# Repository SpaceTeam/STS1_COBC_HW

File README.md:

# COBC Hardware

This is a github repo for the COBC (communication and on-board computer) project of SpaceTeamSat1 (STS1) CubeSat mission of the TU Wien Space Team.

# Licensing
STS1_COBC_HW (c) by TU Wien Space Team

STS1_COBC_HW is licensed under a
Creative Commons Attribution 4.0 International License.

You should have received a copy of the license along with this
work. If not, see <https://creativecommons.org/licenses/by/4.0/>.

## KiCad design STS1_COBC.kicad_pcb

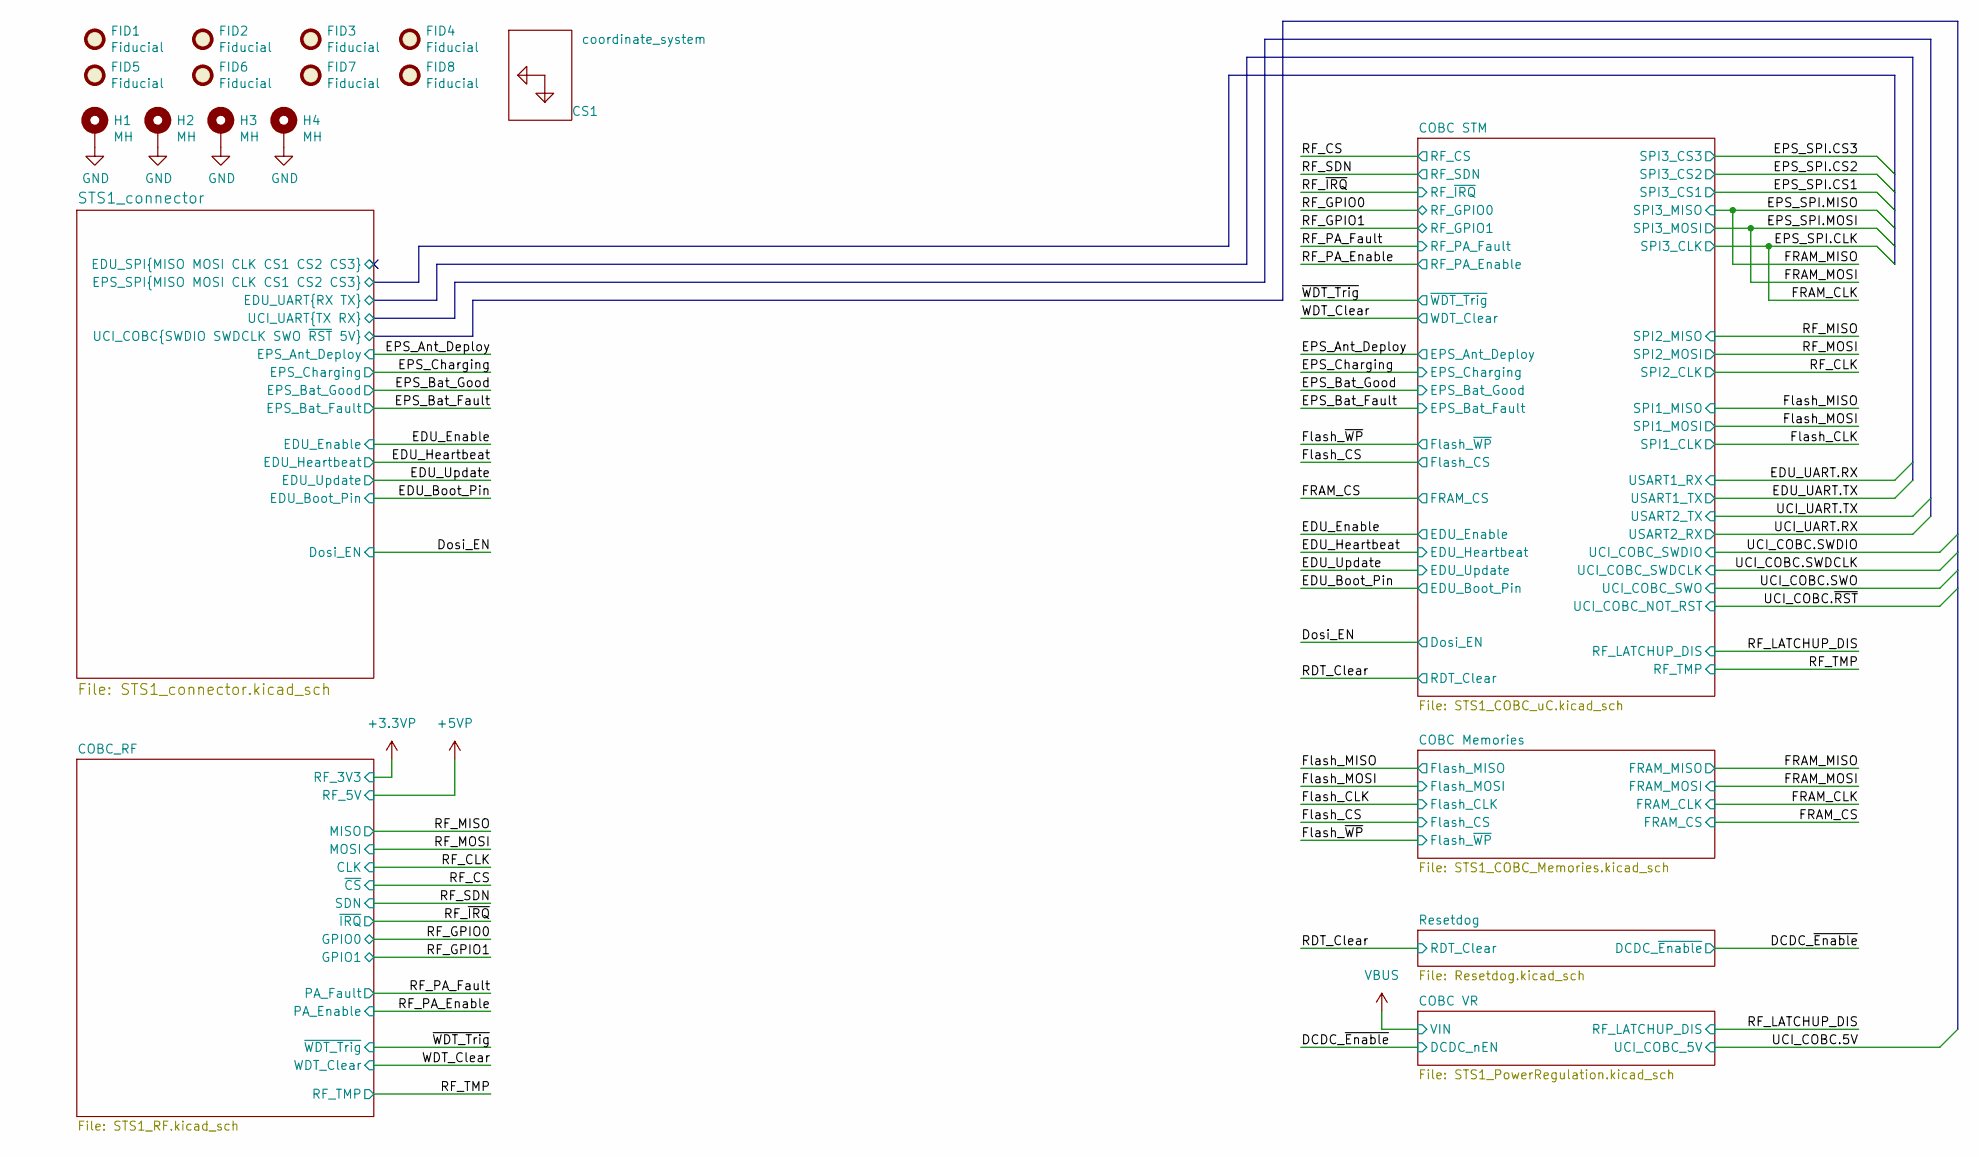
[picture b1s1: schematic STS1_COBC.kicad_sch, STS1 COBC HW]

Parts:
CS1: coordinate_system; Coordinates
FID1, FID2, FID3, FID4, FID5, FID6, FID7, FID8: Fiducial; Fiducial_0.75mm_Mask1.5mm
H1, H2, H3, H4: MH; MountingHole_4.3mm_M4_Pad_Via

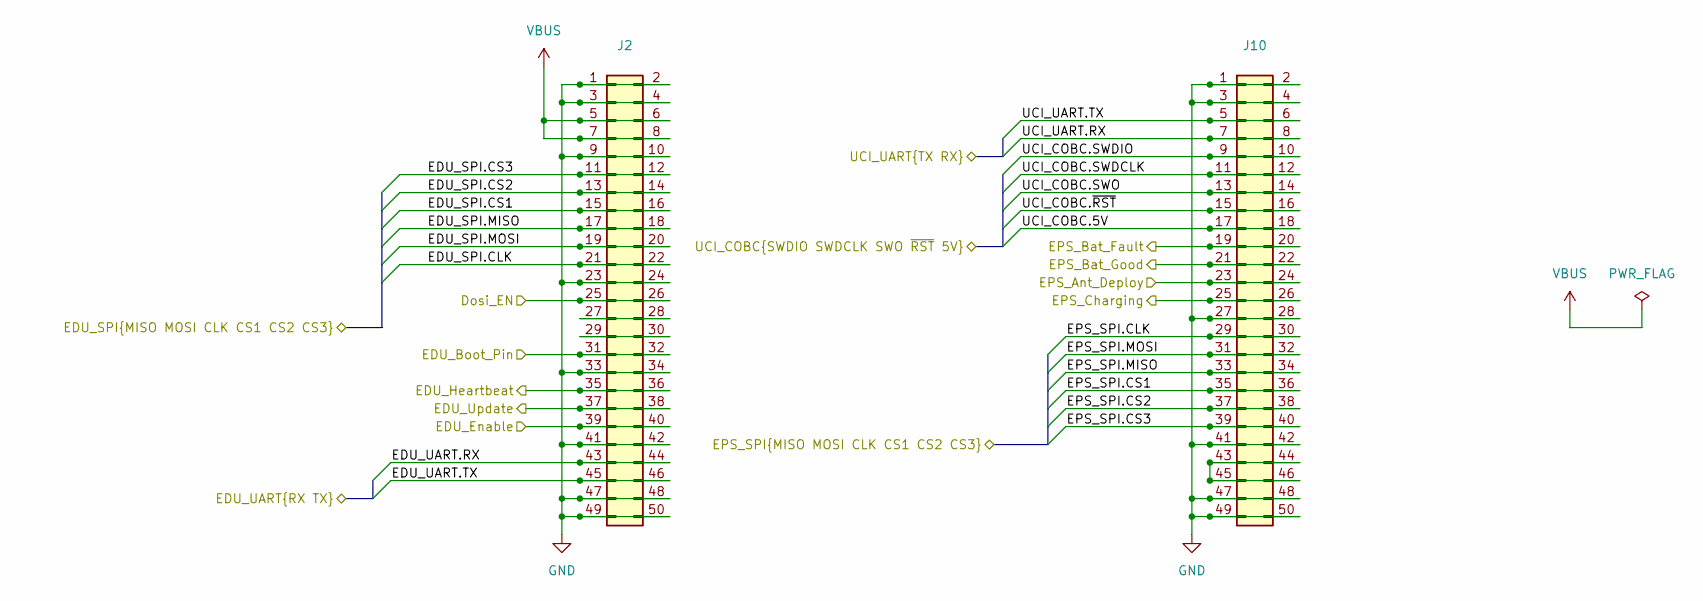
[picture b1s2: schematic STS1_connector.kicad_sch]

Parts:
J2, J10: PinSocket_2x25_P2.00mm_Vertical

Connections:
/Dosi_EN: J2.25, J2.26; also elsewhere on the board
/EDU_Boot_Pin: J2.31, J2.32; also elsewhere on the board
/EDU_Enable: J2.39, J2.40; also elsewhere on the board
/EDU_Heartbeat: J2.35, J2.36; also elsewhere on the board
/EDU_Update: J2.37, J2.38; also elsewhere on the board
/EPS_Ant_Deploy: J10.23, J10.24; also elsewhere on the board
/EPS_Bat_Fault: J10.19, J10.20; also elsewhere on the board
/EPS_Bat_Good: J10.21, J10.22; also elsewhere on the board
/EPS_Charging: J10.25, J10.26; also elsewhere on the board
/STS1_connector/EDU_SPI.CLK: J2.21, J2.22
/STS1_connector/EDU_SPI.CS1: J2.15, J2.16
/STS1_connector/EDU_SPI.CS2: J2.13, J2.14
/STS1_connector/EDU_SPI.CS3: J2.11, J2.12
/STS1_connector/EDU_SPI.MISO: J2.17, J2.18
/STS1_connector/EDU_SPI.MOSI: J2.19, J2.20
/STS1_connector/EDU_UART.RX: J2.43, J2.44; also elsewhere on the board
/STS1_connector/EDU_UART.TX: J2.45, J2.46; also elsewhere on the board
/STS1_connector/EPS_SPI.CLK: J10.29, J10.30; also elsewhere on the board
/STS1_connector/EPS_SPI.CS1: J10.35, J10.36; also elsewhere on the board
/STS1_connector/EPS_SPI.CS2: J10.37, J10.38; also elsewhere on the board
/STS1_connector/EPS_SPI.CS3: J10.39, J10.40; also elsewhere on the board
/STS1_connector/EPS_SPI.MISO: J10.33, J10.34; also elsewhere on the board
/STS1_connector/EPS_SPI.MOSI: J10.31, J10.32; also elsewhere on the board
/STS1_connector/UCI_COBC.5V: J10.17, J10.18; also elsewhere on the board
/STS1_connector/UCI_COBC.SWDCLK: J10.11, J10.12; also elsewhere on the board
/STS1_connector/UCI_COBC.SWDIO: J10.9, J10.10; also elsewhere on the board
/STS1_connector/UCI_COBC.SWO: J10.13, J10.14; also elsewhere on the board
/STS1_connector/UCI_COBC.~RST: J10.15, J10.16; also elsewhere on the board
/STS1_connector/UCI_UART.RX: J10.7, J10.8; also elsewhere on the board
/STS1_connector/UCI_UART.TX: J10.5, J10.6; also elsewhere on the board
unnamed: J2.27, J2.28
unnamed: J2.29, J2.30
unnamed: J10.43, J10.44, J10.45, J10.46

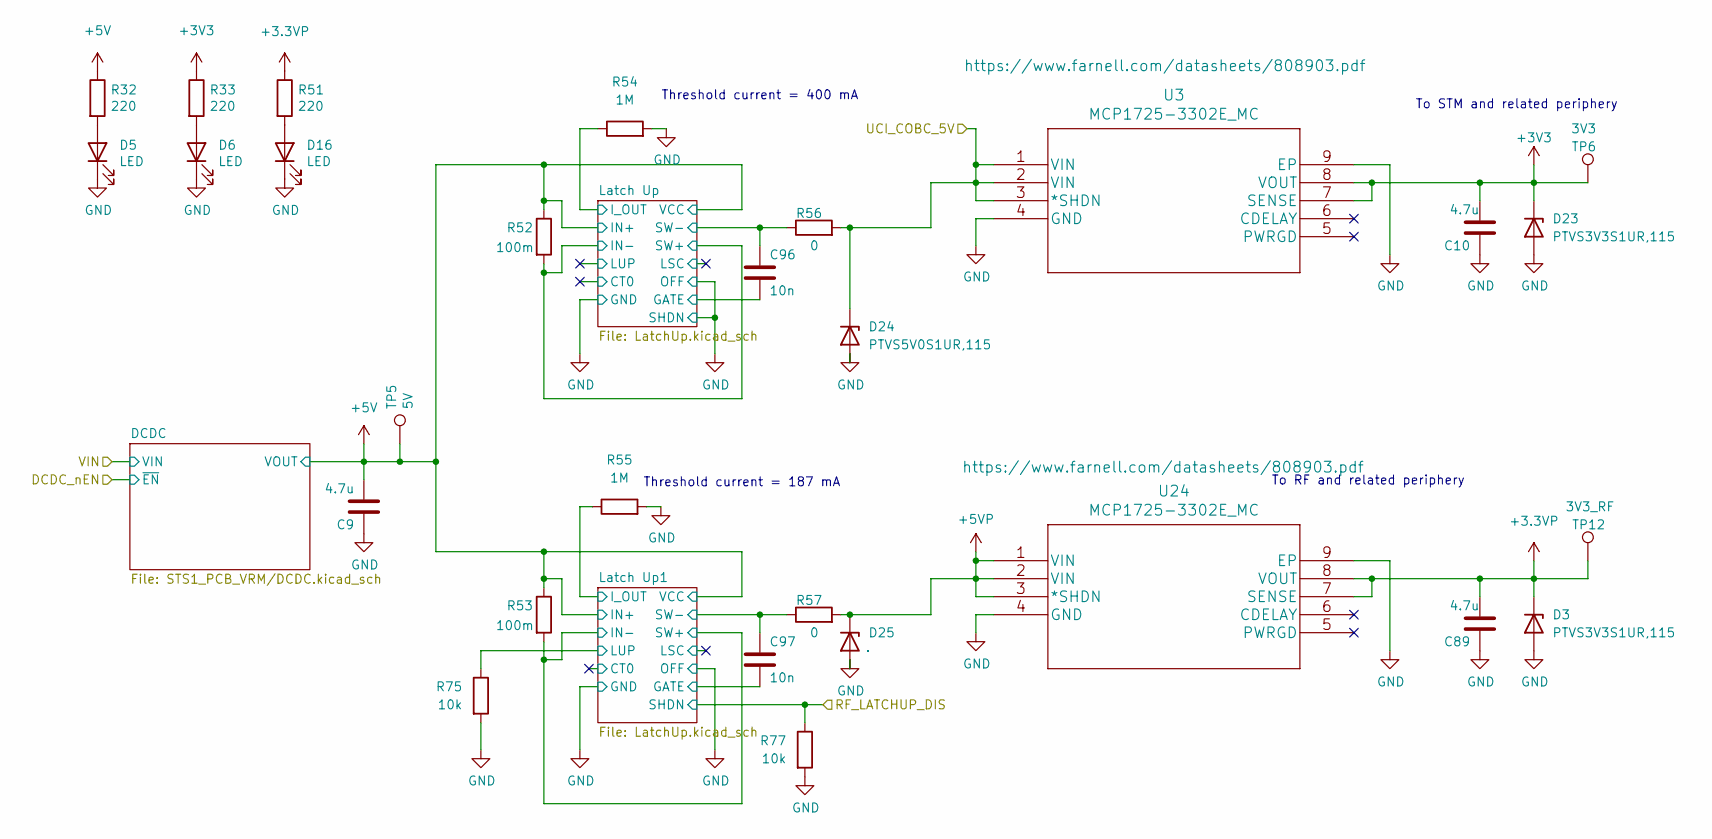
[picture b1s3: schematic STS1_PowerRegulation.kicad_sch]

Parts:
C9, C10, C89: 4.7u; C_0603_1608Metric; Manufacturer_Part_Number CGA3E1X5R0J475KT0Y0E; JLCPCB Part # C338087
C96, C97: 10n; C_0603_1608Metric; Manufacturer_Part_Number C0603C103M5RACAUTO; JLCPCB Part # C2180616
D3, D23: PTVS3V3S1UR,115; D_SOD-123; Manufacturer_Part_Number PTVS3V3S1UR,115; JLCPCB Part # C183521
D5, D6, D16: LED; LED_0805_2012Metric; Manufacturer_Part_Number BL-HGE35A-AV-TRB; JLCPCB Part # C165984
D24, D25: PTVS5V0S1UR,115; D_SOD-123; Manufacturer_Part_Number PTVS5V0S1UR,115; JLCPCB Part # C478011
R32, R33, R51: 220; R_0603_1608Metric; Manufacturer_Part_Number ERJ-H3EF2200V; JLCPCB Part # C4257599
R52, R53: 100m; R_0603_1608Metric; Manufacturer_Part_Number RCWL0603R100JQEA; JLCPCB Part # C1698656
R54, R55: 1M; R_0603_1608Metric; Manufacturer_Part_Number MR06X1004FTL
R56, R57: 0; R_0603_1608Metric; Manufacturer_Part_Number ERJ-H3G0R00V; JLCPCB Part # C4117710
R75, R77: 10k; R_0603_1608Metric; Manufacturer_Part_Number ERJ-H3EF1002V; JLCPCB Part # C4297913
TP5: 5V; STS1_Testpoint
TP6: 3V3; STS1_Testpoint
TP12: 3V3_RF; STS1_Testpoint
U3, U24: MCP1725-3302E_MC; MCP1725-3302E&slash_MC; Manufacturer_Part_Number MCP1725-3302E/MC; JLCPCB Part # C635002

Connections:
+3.3VP: C89.2, D3.1 (K), R51.1, TP12.1 (1_1), U24.7 (SENSE), U24.8 (VOUT); also elsewhere on the board
+5VP: D25.1 (K), R57.2, U24.1 (VIN), U24.2 (VIN), U24.3 (*SHDN); also elsewhere on the board
/COBC VR/Latch Up1/GATE: C97.2; also elsewhere on the board
/COBC VR/Latch Up1/IN-: R53.2; also elsewhere on the board
/COBC VR/Latch Up1/I_OUT: R55.1; also elsewhere on the board
/COBC VR/Latch Up1/LUP: R75.1; also elsewhere on the board
/COBC VR/Latch Up1/SW-: C97.1, R57.1; also elsewhere on the board
/COBC VR/Latch Up/GATE: C96.2; also elsewhere on the board
/COBC VR/Latch Up/IN-: R52.2; also elsewhere on the board
/COBC VR/Latch Up/I_OUT: R54.1; also elsewhere on the board
/COBC VR/Latch Up/SW-: C96.1, R56.1; also elsewhere on the board
/RF_LATCHUP_DIS: R77.1; also elsewhere on the board
/STS1_connector/UCI_COBC.5V: D24.1 (K), R56.2, U3.1 (VIN), U3.2 (VIN), U3.3 (*SHDN); also elsewhere on the board
unnamed: D5.2 (A), R32.2
unnamed: D6.2 (A), R33.2
unnamed: D16.2 (A), R51.2

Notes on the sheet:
Threshold current = 400 mA
Threshold current = 187 mA
To RF and related periphery
To STM and related periphery

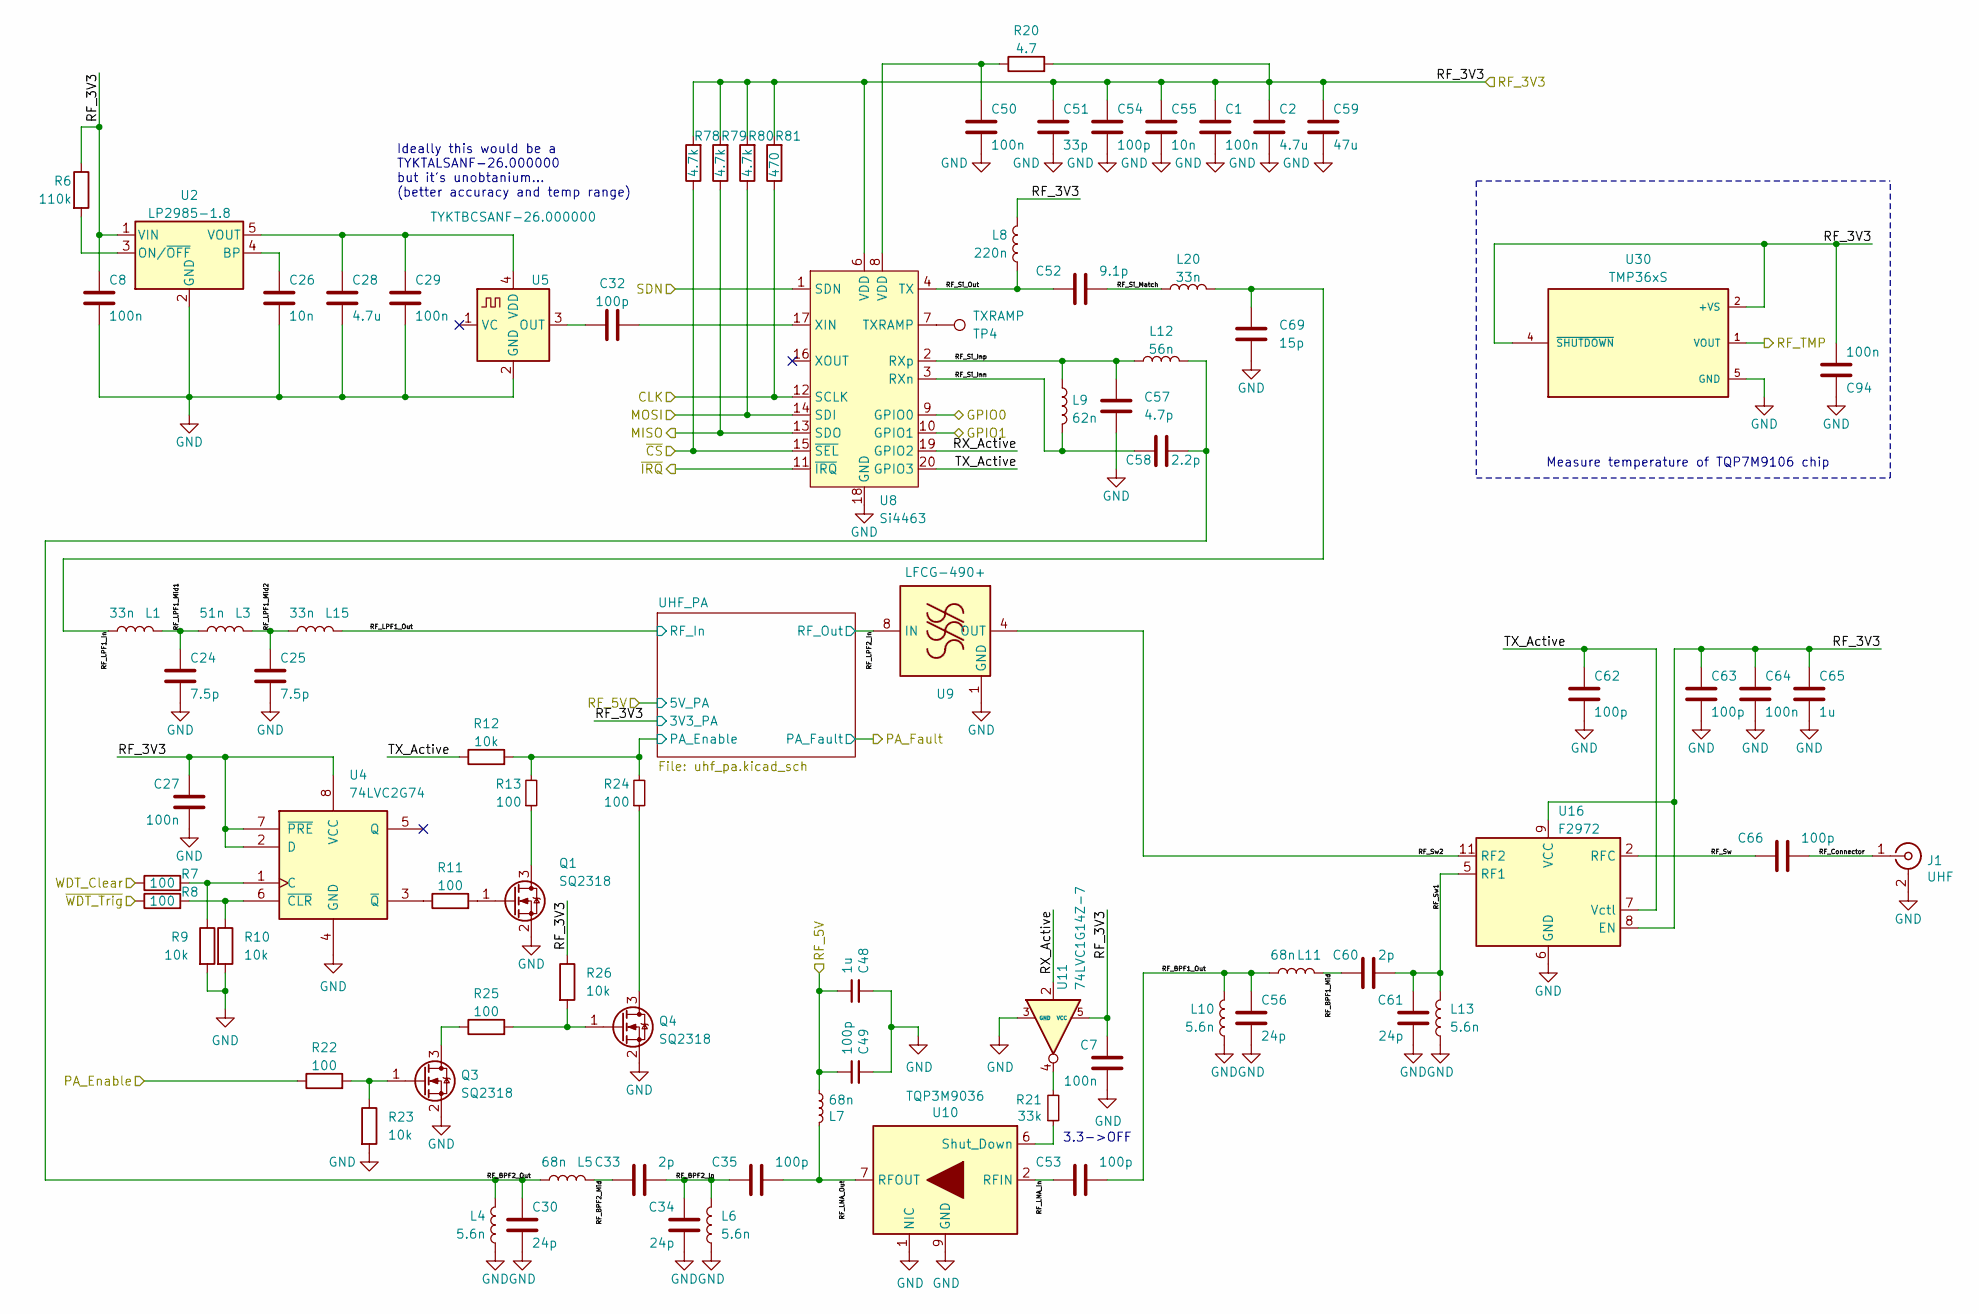
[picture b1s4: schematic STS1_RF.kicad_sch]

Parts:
C1, C7, C8, C27, C29, C50, C64: 100n; C_0805_2012Metric; Manufacturer_Part_Number C0805C104K1RACAUTO; JLCPCB Part # C141125
C2, C28: 4.7u; C_0805_2012Metric; Manufacturer_Part_Number C0805C475K4RACAUTO; JLCPCB Part # C599948
C24, C25: 7.5p; C_0402_1005Metric; Manufacturer_Part_Number VJ0402D7R5CXAAJHT; JLCPCB Part # C3864905
C26, C55: 10n; C_0805_2012Metric; Manufacturer_Part_Number C0805C103K8RACAUTO; JLCPCB Part # C561833
C30, C34, C56, C61: 24p; C_0402_1005Metric; Manufacturer_Part_Number UMK105CG240JV-F; JLCPCB Part # C3833393
C32, C35, C53, C54, C62, C63, C66: 100p; C_0402_1005Metric; Manufacturer_Part_Number UMK105CG101JV-F; JLCPCB Part # C386123
C33, C60: 2p; C_0402_1005Metric; Manufacturer_Part_Number GRM1555C1H2R0CA01D; JLCPCB Part # C76962
C48: 1u; C_0805_2012Metric; PartNumber C0402C105K8PAC7411; JLCPCB Part # C3874210
C49: 100p; C_0402_1005Metric; PartNumber CBR04C101J3GAC; JLCPCB Part # C386123
C51: 33p; C_0402_1005Metric; Manufacturer_Part_Number CL05C330JB5NNNC; JLCPCB Part # C70465
C52: 9.1p; C_0402_1005Metric; Manufacturer_Part_Number RF15N9R1B500CT; JLCPCB Part # C3908063
C57: 4.7p; C_0402_1005Metric; Manufacturer_Part_Number 885392005012; JLCPCB Part # C5534411
C58: 2.2p; C_0402_1005Metric; Manufacturer_Part_Number RF15N2R2B500CT; JLCPCB Part # C172819
C59: 47u; C_0805_2012Metric; Manufacturer_Part_Number T58W9476M6R3C0200; JLCPCB Part # C3008877
C65: 1u; C_0805_2012Metric; Manufacturer_Part_Number C0805C105K5RACAUTO; JLCPCB Part # C3874210
C69: 15p; C_0402_1005Metric; Manufacturer_Part_Number CC0402FRNPO9BN150; JLCPCB Part # C326803
C94: 100n; C_0603_1608Metric; Manufacturer_Part_Number C0603C104K5RACAUTO; JLCPCB Part # C129621
J1: UHF; SMB_Jack_Vertical; Manufacturer_Part_Number 61612002121503; JLCPCB Part # C6095037
L1, L15, L20: 33n; L_0402_1005Metric; PartNumber LQW15AN33NJ8ZD; JLCPCB Part # C2043918
L3: 51n; L_0402_1005Metric; PartNumber LQW15AN51NG80D
L4, L6, L10, L13: 5.6n; L_0402_1005Metric; PartNumber LQW15AN5N6C1ZD
L5, L7, L11: 68n; L_0402_1005Metric; PartNumber LQW15AN68NJ0ZD; JLCPCB Part # C2049784
L8: 220n; L_0402_1005Metric; PartNumber LQW15CNR22J10D; JLCPCB Part # C341690
L9: 62n; L_0402_1005Metric; PartNumber LQW15AN62NJ0ZD
L12: 56n; L_0402_1005Metric; PartNumber LQW15AN56NH0ZD
Q1, Q3, Q4: SQ2318; SOT-23; Manufacturer_Part_Number SQ2318AES-T1_BE3; JLCPCB Part # C3280170
R6: 110k; R_0603_1608Metric; Manufacturer_Part_Number ERJ-H3EF1103V; JLCPCB Part # C4176290
R7, R8, R11, R13, R22, R24, R25: 100; R_0603_1608Metric; Manufacturer_Part_Number CRS0603AFX-1000ELF; JLCPCB Part # C2074896
R9, R10, R12, R23, R26: 10k; R_0603_1608Metric; Manufacturer_Part_Number ERJ-H3EF1002V; JLCPCB Part # C4297913
R20: 4.7; R_0603_1608Metric; Manufacturer_Part_Number CHP0603QFW-4R70ELF
R21: 33k; R_0603_1608Metric; Manufacturer_Part_Number ERJ-H3EF3302V; JLCPCB Part # C4220470
R78, R79, R80: 4.7k; R_0603_1608Metric; Manufacturer_Part_Number ERJ-H3EF4701V; JLCPCB Part # C4343266
R81: 470; R_0603_1608Metric; Manufacturer_Part_Number ERJ-3EKF4700V; JLCPCB Part # C169259
TP4: TXRAMP; STS1_Testpoint
U2: LP2985-1.8; SOT-23-5; Manufacturer_Part_Number LP2985-18DBVRE4; JLCPCB Part # C3752498
U4: 74LVC2G74; VSSOP-8_2.3x2mm_P0.5mm; Manufacturer_Part_Number SN74LVC2G74DCUTE4; JLCPCB Part # C3826121
U5: TYKTBCSANF-26.000000; Crystal_SMD_2520-4Pin_2.5x2.0mm; Manufacturer_Part_Number TYKTBCSANF-26.000000; JLCPCB Part # C6304737
U8: Si4463; QFN-20-1EP_4x4mm_P0.5mm_EP2.6x2.6mm_ThermalVias; Manufacturer_Part_Number SI4463-C2A-GM; JLCPCB Part # C476202
U9: LFCG-490+; GE0805C-2; PartNumber LFCG-490+; JLCPCB Part # C3034233
U10: TQP3M9036; DFN-8-1EP_2x2mm_P0.5mm_EP0.7x1.6mm_ThermalVias; PartNumber TQP3M9036; JLCPCB Part # C920261
U11: 74LVC1G14Z-7; SOT-553; PartNumber NL17SV04XV5T2G; JLCPCB Part # C3272831
U16: F2972; IDT_NEG-12-1EP_2x2mm_P0.5mm_EP1.1x1.1mm_ThermalVias; Manufacturer_Part_Number F2972NEGK; JLCPCB Part # C1558621
U30: TMP36xS; SOT-23-5; PARTREV H; JLCPCB Part # C129489

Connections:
+3.3VP: C1.1, C2.1, C7.1, C8.1, C27.1, C51.1, C54.1, C55.1, C59.1, C63.1, C64.1, C65.1, C94.2, L8.2, R6.1, R20.2, R26.1, R78.2, R79.2, R80.2, R81.2, U2.1 (VIN), U4.2 (D), U4.7 (~PRE), U4.8 (VCC), U8.6 (VDD), U11.5 (VCC), U16.8 (EN), U16.9 (VCC), U30.2 (+VS), U30.4 (~SHUTDOWN); also elsewhere on the board
+5VP: C48.1, C49.1, L7.2; also elsewhere on the board
/COBC_RF/RF_BPF1_Mid: C60.1, L11.2
/COBC_RF/RF_BPF1_Out: C53.2, C56.1, L10.2, L11.1
/COBC_RF/RF_BPF2_In: C33.2, C34.1, C35.1, L6.2
/COBC_RF/RF_BPF2_Mid: C33.1, L5.2
/COBC_RF/RF_BPF2_Out: C30.1, C58.2, L4.2, L5.1, L12.2
/COBC_RF/RF_Connector: C66.2, J1.1 (In)
/COBC_RF/RF_LNA_In: C53.1, U10.2 (RFIN)
/COBC_RF/RF_LNA_Out: C35.2, L7.1, U10.7 (RFOUT)
/COBC_RF/RF_LPF1_In: C69.1, L1.1, L20.2
/COBC_RF/RF_LPF1_Mid1: C24.1, L1.2, L3.1
/COBC_RF/RF_LPF1_Mid2: C25.1, L3.2, L15.1
/COBC_RF/RF_LPF1_Out: L15.2; also elsewhere on the board
/COBC_RF/RF_LPF2_In: U9.8 (IN); also elsewhere on the board
/COBC_RF/RF_Si_Inn: C58.1, L9.2, U8.3 (RXn)
/COBC_RF/RF_Si_Inp: C57.1, L9.1, L12.1, U8.2 (RXp)
/COBC_RF/RF_Si_Match: C52.2, L20.1
/COBC_RF/RF_Si_Out: C52.1, L8.1, U8.4 (TX)
/COBC_RF/RF_Sw: C66.1, U16.2 (RFC)
/COBC_RF/RF_Sw1: C60.2, C61.1, L13.2, U16.5 (RF1)
/COBC_RF/RF_Sw2: U9.4 (OUT), U16.11 (RF2)
/COBC_RF/RX_Active: U8.19 (GPIO2), U11.2
/COBC_RF/TX_Active: C62.1, R12.1, U8.20 (GPIO3), U16.7 (Vctl)
/COBC_RF/UHF_PA/PA_Enable: R12.2, R13.2, R24.2; also elsewhere on the board
/RF_CLK: R81.1, U8.12 (SCLK); also elsewhere on the board
/RF_CS: R78.1, U8.15 (~SEL); also elsewhere on the board
/RF_GPIO0: U8.9 (GPIO0); also elsewhere on the board
/RF_GPIO1: U8.10 (GPIO1); also elsewhere on the board
/RF_MISO: R79.1, U8.13 (SDO); also elsewhere on the board
/RF_MOSI: R80.1, U8.14 (SDI); also elsewhere on the board
/RF_PA_Enable: R22.1; also elsewhere on the board
/RF_SDN: U8.1 (SDN); also elsewhere on the board
/RF_TMP: U30.1 (VOUT); also elsewhere on the board
/RF_~IRQ: U8.11 (~IRQ); also elsewhere on the board
/WDT_Clear: R7.1; also elsewhere on the board
/~WDT_Trig: R8.1; also elsewhere on the board
unnamed: C50.1, R20.1, U8.8 (VDD)
unnamed: Q1.3 (D), R13.1
unnamed: Q1.1 (G), R11.2
unnamed: Q3.3 (D), R25.1
unnamed: Q3.1 (G), R22.2, R23.1
unnamed: Q4.3 (D), R24.1
unnamed: Q4.1 (G), R25.2, R26.2
unnamed: R21.2, U11.4
unnamed: C26.1, U2.4 (BP)
unnamed: R6.2, U2.3 (ON/~OFF)
unnamed: C28.1, C29.1, U2.5 (VOUT), U5.4 (VDD)
unnamed: R7.2, R9.1, U4.1 (C)
unnamed: R8.2, R10.1, U4.6 (~CLR)
unnamed: R11.1, U4.3 (~Q)
unnamed: C32.1, U5.3 (OUT)
unnamed: TP4.1 (1_1), U8.7 (TXRAMP)
unnamed: C32.2, U8.17 (XIN)
unnamed: R21.1, U10.6 (Shut_Down)

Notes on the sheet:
3.3->OFF
Ideally this would be a TYKTALSANF-26.000000 but it's unobtanium... (better accuracy and temp range)
Measure temperature of TQP7M9106 chip

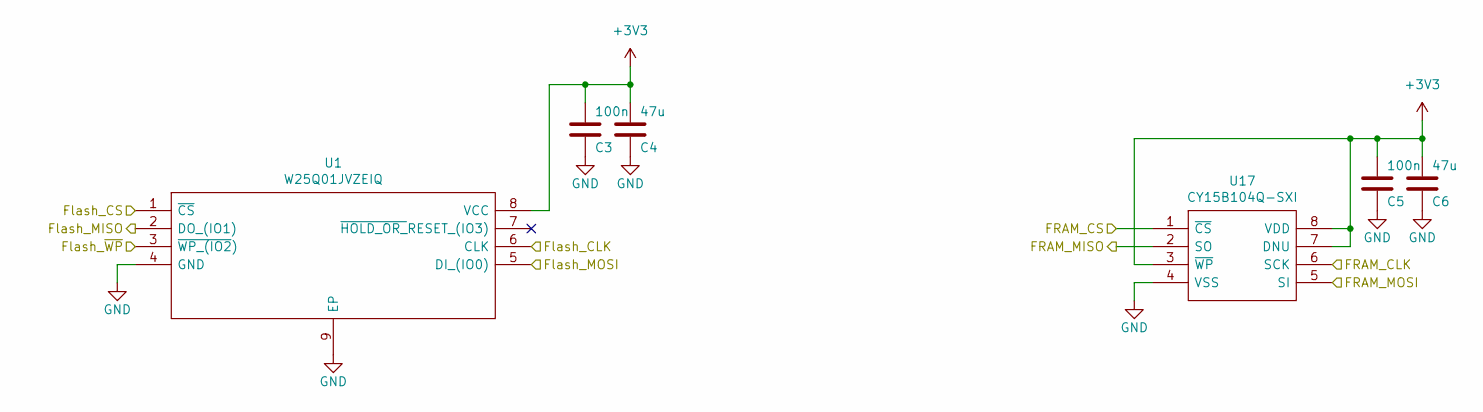
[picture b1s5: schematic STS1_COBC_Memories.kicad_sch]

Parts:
C3, C5: 100n; C_0603_1608Metric; Manufacturer_Part_Number C0603C104K5RACAUTO; JLCPCB Part # C129621
C4, C6: 47u; C_0603_1608Metric; Manufacturer_Part_Number CL10A476MQ8QRNC; JLCPCB Part # C730416
U1: W25Q01JVZEIQ; SON127P800X600X80-9N-D; Manufacturer_Part_Number W25Q01JVZEIQ; Mouser Part Number 454-W25Q01JVZEIQ
U17: CY15B104Q-SXI; SOIC127P800X203-8N; Manufacturer_Part_Number CY15B104Q-SXI; Mouser Part Number 727-CY15B104Q-SXI

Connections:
/FRAM_CS: U17.1 (~CS); also elsewhere on the board
/Flash_CLK: U1.6 (CLK); also elsewhere on the board
/Flash_CS: U1.1 (~CS); also elsewhere on the board
/Flash_MISO: U1.2 (DO_(IO1)); also elsewhere on the board
/Flash_MOSI: U1.5 (DI_(IO0)); also elsewhere on the board
/Flash_~WP: U1.3 (~WP_(IO2)); also elsewhere on the board
/STS1_connector/EPS_SPI.CLK: U17.6 (SCK); also elsewhere on the board
/STS1_connector/EPS_SPI.MISO: U17.2 (SO); also elsewhere on the board
/STS1_connector/EPS_SPI.MOSI: U17.5 (SI); also elsewhere on the board

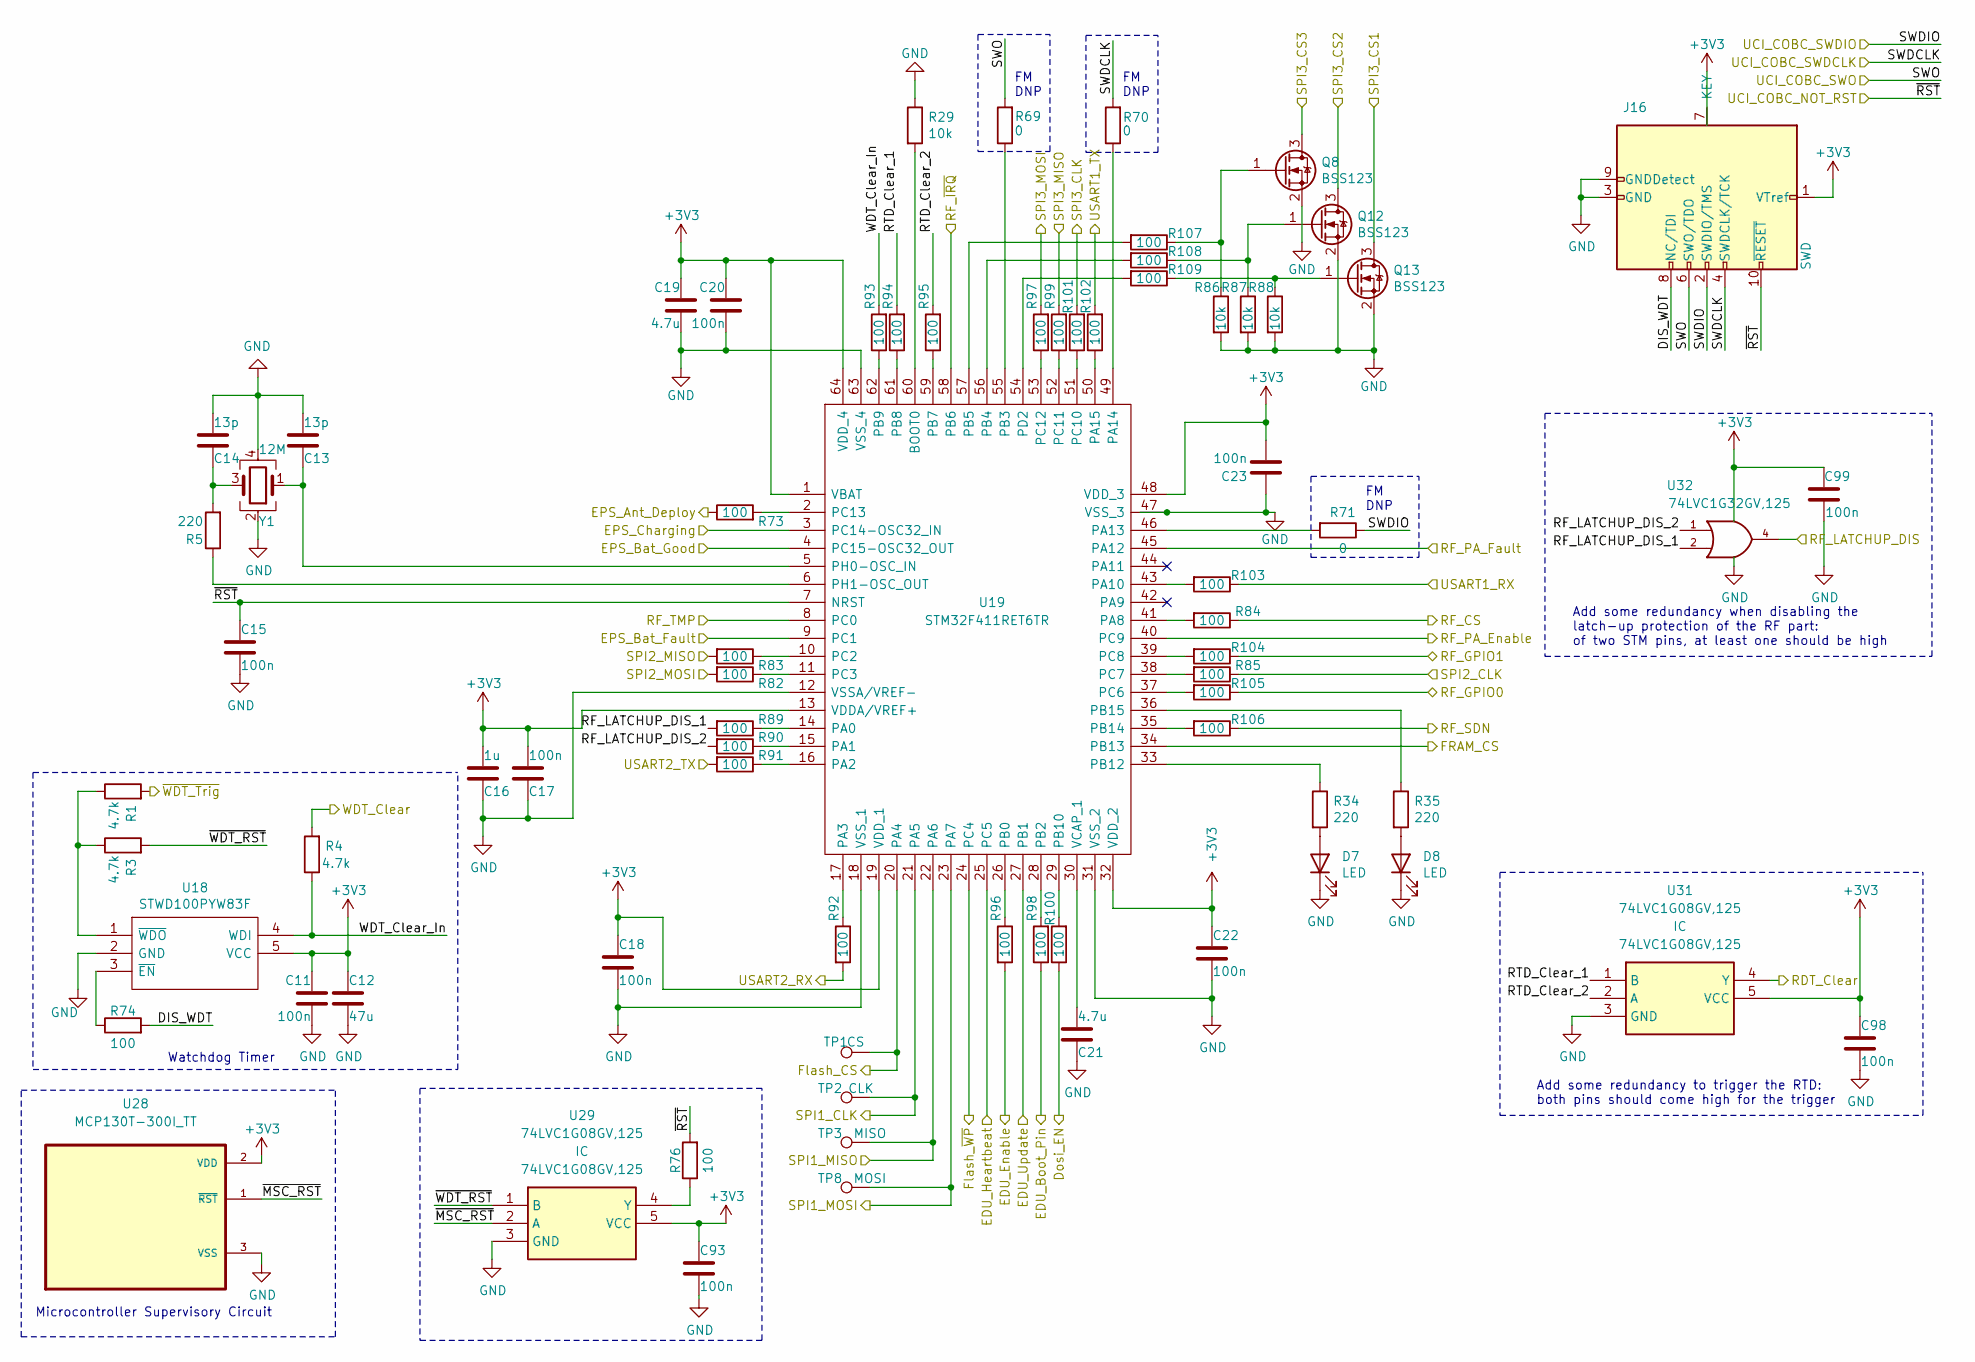
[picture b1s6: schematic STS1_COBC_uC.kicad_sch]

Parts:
C11, C15, C17, C18, C20, C22, C23, C93, C98, C99: 100n; C_0603_1608Metric; Manufacturer_Part_Number C0603C104K5RACAUTO; JLCPCB Part # C129621
C12: 47u; C_0603_1608Metric; Manufacturer_Part_Number CL10A476MQ8QRNC; JLCPCB Part # C730416
C13, C14: 13p; C_0603_1608Metric; Manufacturer_Part_Number CC0603FRNPO9BN130; JLCPCB Part # C519488
C16: 1u; C_0603_1608Metric; Manufacturer_Part_Number CGA3E1X7R1V105KT000N; JLCPCB Part # C342956
C19, C21: 4.7u; C_0603_1608Metric; Manufacturer_Part_Number CGA3E1X5R0J475KT0Y0E; JLCPCB Part # C338087
D7, D8: LED; LED_0805_2012Metric; Manufacturer_Part_Number BL-HGE35A-AV-TRB; JLCPCB Part # C165984
J16: SWD; SAMTEC_FTSH-105-01-X-DH-A; Manufacturer_Part_Number FTSH-105-01-F-DH-A
Q8, Q12, Q13: BSS123; SOT-23; Manufacturer_Part_Number BSS123N H6327; JLCPCB Part # C534594
R1, R3, R4: 4.7k; R_0603_1608Metric; Manufacturer_Part_Number ERJ-H3EF4701V; JLCPCB Part # C4343266
R5, R34, R35: 220; R_0603_1608Metric; Manufacturer_Part_Number ERJ-H3EF2200V; JLCPCB Part # C4257599
R29, R86, R87, R88: 10k; R_0603_1608Metric; Manufacturer_Part_Number ERJ-H3EF1002V; JLCPCB Part # C4297913
R69, R70, R71: 0; R_0603_1608Metric; Manufacturer_Part_Number ERJ-H3G0R00V; JLCPCB Part # C4117710
R73, R74, R76, R82, R83, R84, R85, R89, R90, R91, R92, R93, R94, R95, R96, R97, R98, R99, R100, R101, R102, R103, R104, R105, R106, R107, R108, R109: 100; R_0603_1608Metric; Manufacturer_Part_Number CRS0603AFX-1000ELF; JLCPCB Part # C2074896
TP1: CS; STS1_Testpoint
TP2: CLK; STS1_Testpoint
TP3: MISO; STS1_Testpoint
TP8: MOSI; STS1_Testpoint
U18: STWD100PYW83F; SOT65P210X110-5N; Manufacturer_Part_Number STWD100PYW83F; JLCPCB Part # C155589
U19: STM32F411RET6TR; QFP50P1200X1200X160-64N; Manufacturer_Part_Number STM32F411RET6TR; Mouser Part Number 511-STM32F411RET6TR
U28: MCP130T-300I_TT; SOT-23-3; Manufacturer_Part_Number MCP130T-300I/TT; JLCPCB Part # C410526
U29, U31: 74LVC1G08GV,125; SOT95P275X110-5N; Mouser Part Number 771-74LVC1G08GV
U32: 74LVC1G32GV,125; SOT95P275X110-5N; Manufacturer_Part_Number 74LVC1G32GV,125; JLCPCB Part # C12517
Y1: 12M; Crystal_SMD_5032-4Pin_5.0x3.2mm; Manufacturer_Part_Number 405C35B12M00000; JLCPCB Part # C1986181

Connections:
/COBC STM/DIS_WDT: J16.8 (NC/TDI), R74.2
/COBC STM/RF_LATCHUP_DIS_1: R89.2, U32.2
/COBC STM/RF_LATCHUP_DIS_2: R90.2, U32.1
/COBC STM/RTD_Clear_1: R94.2, U31.1 (B)
/COBC STM/RTD_Clear_2: R95.2, U31.2 (A)
/COBC STM/WDT_Clear_In: R4.1, R93.2, U18.4 (WDI)
/COBC STM/~MSC_RST: U28.1 (~RST), U29.2 (A)
/COBC STM/~WDT_RST: R3.2, U29.1 (B)
/Dosi_EN: R100.1; also elsewhere on the board
/EDU_Boot_Pin: R98.1; also elsewhere on the board
/EDU_Enable: R96.2; also elsewhere on the board
/EDU_Heartbeat: U19.25 (PC5); also elsewhere on the board
/EDU_Update: U19.27 (PB1); also elsewhere on the board
/EPS_Ant_Deploy: R73.1; also elsewhere on the board
/EPS_Bat_Fault: U19.9 (PC1); also elsewhere on the board
/EPS_Bat_Good: U19.4 (PC15-OSC32_OUT); also elsewhere on the board
/EPS_Charging: U19.3 (PC14-OSC32_IN); also elsewhere on the board
/FRAM_CS: U19.34 (PB13); also elsewhere on the board
/Flash_CLK: TP2.1 (1_1), U19.21 (PA5); also elsewhere on the board
/Flash_CS: TP1.1 (1_1), U19.20 (PA4); also elsewhere on the board
/Flash_MISO: TP3.1 (1_1), U19.22 (PA6); also elsewhere on the board
/Flash_MOSI: TP8.1 (1_1), U19.23 (PA7); also elsewhere on the board
/Flash_~WP: U19.24 (PC4); also elsewhere on the board
/RDT_Clear: U31.4 (Y); also elsewhere on the board
/RF_CLK: R85.1; also elsewhere on the board
/RF_CS: R84.1; also elsewhere on the board
/RF_GPIO0: R105.1; also elsewhere on the board
/RF_GPIO1: R104.1; also elsewhere on the board
/RF_LATCHUP_DIS: U32.4; also elsewhere on the board
/RF_MISO: R83.2; also elsewhere on the board
/RF_MOSI: R82.2; also elsewhere on the board
/RF_PA_Enable: U19.40 (PC9); also elsewhere on the board
/RF_PA_Fault: U19.45 (PA12); also elsewhere on the board
/RF_SDN: R106.1; also elsewhere on the board
/RF_TMP: U19.8 (PC0); also elsewhere on the board
/RF_~IRQ: U19.58 (PB6); also elsewhere on the board
/STS1_connector/EDU_UART.RX: R103.1; also elsewhere on the board
/STS1_connector/EDU_UART.TX: R102.2; also elsewhere on the board
/STS1_connector/EPS_SPI.CLK: R101.2; also elsewhere on the board
/STS1_connector/EPS_SPI.CS1: Q13.3 (D); also elsewhere on the board
/STS1_connector/EPS_SPI.CS2: Q12.3 (D); also elsewhere on the board
/STS1_connector/EPS_SPI.CS3: Q8.3 (D); also elsewhere on the board
/STS1_connector/EPS_SPI.MISO: R99.2; also elsewhere on the board
/STS1_connector/EPS_SPI.MOSI: R97.2; also elsewhere on the board
/STS1_connector/UCI_COBC.SWDCLK: J16.4 (SWDCLK/TCK), R70.2; also elsewhere on the board
/STS1_connector/UCI_COBC.SWDIO: J16.2 (SWDIO/TMS), R71.1; also elsewhere on the board
/STS1_connector/UCI_COBC.SWO: J16.6 (SWO/TDO), R69.2; also elsewhere on the board
/STS1_connector/UCI_COBC.~RST: C15.2, J16.10 (~RESET), R76.2, U19.7 (NRST); also elsewhere on the board
/STS1_connector/UCI_UART.RX: R92.2; also elsewhere on the board
/STS1_connector/UCI_UART.TX: R91.2; also elsewhere on the board
/WDT_Clear: R4.2; also elsewhere on the board
/~WDT_Trig: R1.2; also elsewhere on the board
unnamed: C14.2, R5.2, Y1.3
unnamed: D7.2 (A), R34.2
unnamed: D8.2 (A), R35.2
unnamed: Q8.1 (G), R86.1, R107.1
unnamed: Q12.1 (G), R87.1, R108.1
unnamed: Q13.1 (G), R88.1, R109.1
unnamed: R74.1, U18.3 (~EN)
unnamed: R1.1, R3.1, U18.1 (~WDO)
unnamed: R29.2, U19.60 (BOOT0)
unnamed: R89.1, U19.14 (PA0)
unnamed: R90.1, U19.15 (PA1)
unnamed: R91.1, U19.16 (PA2)
unnamed: R92.1, U19.17 (PA3)
unnamed: R84.2, U19.41 (PA8)
unnamed: R103.2, U19.43 (PA10)
unnamed: R71.2, U19.46 (PA13)
unnamed: R70.1, U19.49 (PA14)
unnamed: R102.1, U19.50 (PA15)
unnamed: R96.1, U19.26 (PB0)
unnamed: R98.2, U19.28 (PB2)
unnamed: R69.1, U19.55 (PB3)
unnamed: R108.2, U19.56 (PB4)
unnamed: R107.2, U19.57 (PB5)
unnamed: R95.1, U19.59 (PB7)
unnamed: R94.1, U19.61 (PB8)
unnamed: R93.1, U19.62 (PB9)
unnamed: R100.2, U19.29 (PB10)
unnamed: R34.1, U19.33 (PB12)
unnamed: R106.2, U19.35 (PB14)
unnamed: R35.1, U19.36 (PB15)
unnamed: R83.1, U19.10 (PC2)
unnamed: R82.1, U19.11 (PC3)
unnamed: R105.2, U19.37 (PC6)
unnamed: R85.2, U19.38 (PC7)
unnamed: R104.2, U19.39 (PC8)
unnamed: R101.1, U19.51 (PC10)
unnamed: R99.1, U19.52 (PC11)
unnamed: R97.1, U19.53 (PC12)
unnamed: R73.2, U19.2 (PC13)
unnamed: R109.2, U19.54 (PD2)
unnamed: C13.2, U19.5 (PH0-OSC_IN), Y1.1
unnamed: R5.1, U19.6 (PH1-OSC_OUT)
unnamed: C21.1, U19.30 (VCAP_1)
unnamed: R76.1, U29.4 (Y)

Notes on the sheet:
Add some redundancy to trigger the RTD: both pins should come high for the trigger
Microcontroller Supervisory Circuit
FM DNP
Add some redundancy when disabling the latch-up protection of the RF part: of two STM pins, at least one should be high
Watchdog Timer

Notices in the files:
parts and their libraries:
COPYRIGHT: Copyright C 2016 Accelerated Designs. All rights reserved
Copyright C 2016 Accelerated Designs. All rights reserved
Copyright 2021 Accelerated Designs. All rights reserved.
